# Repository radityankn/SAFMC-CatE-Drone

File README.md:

# SAFMC-CatE-Drone
A repository for SAFMC Cat E 2025 Drone Design. It consist of Hardware, Software, and Firmware file. The drone is incomplete though, as lack of funds and increased difficulty of development continue to prevent the team from completing it, leading to its early withdrawal from the competition

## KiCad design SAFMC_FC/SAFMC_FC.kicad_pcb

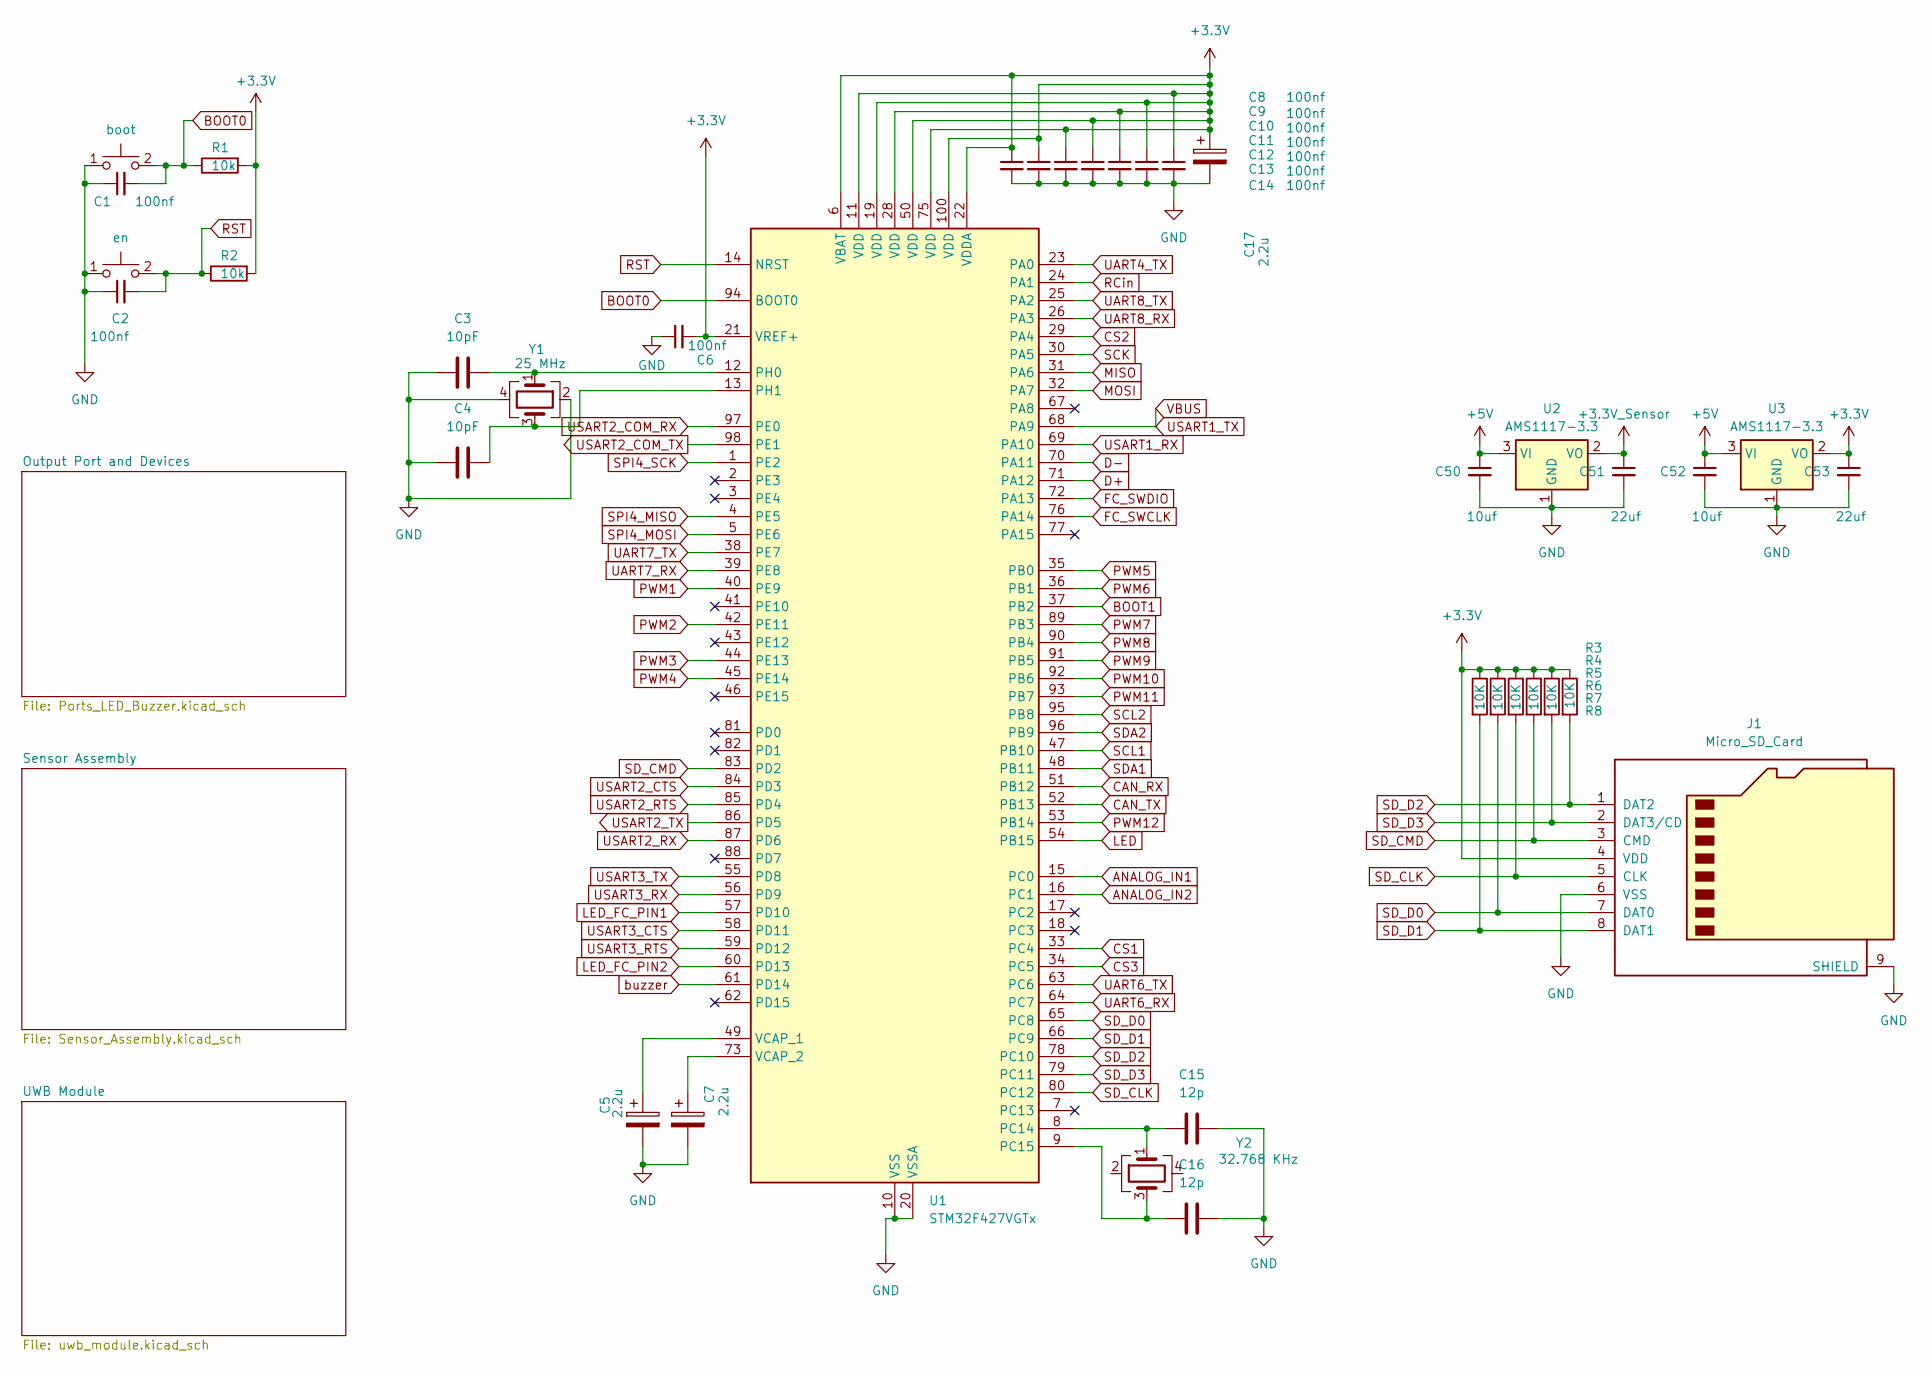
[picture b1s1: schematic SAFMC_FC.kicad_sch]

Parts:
C1, C2, C6, C8, C9, C10, C11, C12, C13, C14: 100nf; C_0603_1608Metric_Pad1.08x0.95mm_HandSolder
C3, C4: 10pF; C_0603_1608Metric_Pad1.08x0.95mm_HandSolder
C5, C7, C17: 2.2u; C_0603_1608Metric_Pad1.08x0.95mm_HandSolder
C15, C16: 12p; C_0603_1608Metric_Pad1.08x0.95mm_HandSolder
C50, C52: 10uf; C_0805_2012Metric_Pad1.18x1.45mm_HandSolder
C51, C53: 22uf; C_0805_2012Metric_Pad1.18x1.45mm_HandSolder
J1: Micro_SD_Card; microSD_HC_Hirose_DM3BT-DSF-PEJS
R1, R2: 10k; R_0603_1608Metric_Pad0.98x0.95mm_HandSolder
R3, R4, R5, R6, R7, R8: 10K; R_0603_1608Metric_Pad0.98x0.95mm_HandSolder
SW1: boot; SW_Push_SPST_NO_Alps_SKRK
SW2: en; SW_Push_SPST_NO_Alps_SKRK
U1: STM32F427VGTx; LQFP-100_14x14mm_P0.5mm
U2, U3: AMS1117-3.3; SOT-223-3_TabPin2
Y1: 25 MHz; Crystal_SMD_3225-4Pin_3.2x2.5mm_HandSoldering
Y2: 32.768 KHz; Crystal_SMD_SeikoEpson_MC306-4Pin_8.0x3.2mm

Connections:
+3.3V: C6.2, C8.1, C9.1, C10.1, C11.1, C12.1, C13.1, C14.1, C17.1, C53.1, J1.4 (VDD), R1.1, R2.1, R3.1, R4.1, R5.1, R6.1, R7.1, R8.1, U1.6 (VBAT), U1.11 (VDD), U1.19 (VDD), U1.21 (VREF+), U1.22 (VDDA), U1.28 (VDD), U1.50 (VDD), U1.75 (VDD), U1.100 (VDD), U3.2 (VO); also elsewhere on the board
+3.3V_Sensor: C51.1, U2.2 (VO); also elsewhere on the board
+5V: C50.1, C52.1, U2.3 (VI), U3.3 (VI); also elsewhere on the board
ANALOG_IN1: U1.15 (PC0)
ANALOG_IN2: U1.16 (PC1)
BOOT0: C1.2, R1.2, SW1.2 (D), U1.94 (BOOT0)
BOOT1: U1.37 (PB2)
CAN_RX: U1.51 (PB12)
CAN_TX: U1.52 (PB13)
CS1: U1.33 (PC4); also elsewhere on the board
CS2: U1.29 (PA4); also elsewhere on the board
CS3: U1.34 (PC5); also elsewhere on the board
D+: U1.71 (PA12); also elsewhere on the board
D-: U1.70 (PA11); also elsewhere on the board
FC_SWCLK: U1.76 (PA14)
FC_SWDIO: U1.72 (PA13)
GND: C1.1, C2.1, C3.1, C4.1, C5.2, C6.1, C7.2, C8.2, C9.2, C10.2, C11.2, C12.2, C13.2, C14.2, C15.1, C16.1, C17.2, C50.2, C51.2, C52.2, C53.2, J1.6 (VSS), J1.9 (SHIELD), J1.11, SW1.1 (C), SW2.1 (C), U1.10 (VSS), U1.20 (VSSA), U1.27 (VSS), U1.74 (VSS), U1.99 (VSS), U2.1 (GND), U3.1 (GND), Y1.2, Y1.4; also elsewhere on the board
LED: U1.54 (PB15); also elsewhere on the board
LED_FC_PIN1: U1.57 (PD10); also elsewhere on the board
LED_FC_PIN2: U1.60 (PD13); also elsewhere on the board
MISO: U1.31 (PA6); also elsewhere on the board
MOSI: U1.32 (PA7); also elsewhere on the board
unnamed: C15.2, U1.8 (PC14), Y2.1
unnamed: C16.2, U1.9 (PC15), Y2.3
unnamed: C3.2, U1.12 (PH0), Y1.1
unnamed: C4.2, U1.13 (PH1), Y1.3
unnamed: C5.1, U1.49 (VCAP_1)
unnamed: C7.1, U1.73 (VCAP_2)
PWM1: U1.40 (PE9); also elsewhere on the board
PWM2: U1.42 (PE11); also elsewhere on the board
PWM3: U1.44 (PE13); also elsewhere on the board
PWM4: U1.45 (PE14); also elsewhere on the board
PWM5: U1.35 (PB0); also elsewhere on the board
PWM6: U1.36 (PB1); also elsewhere on the board
PWM7: U1.89 (PB3)
PWM8: U1.90 (PB4)
PWM9: U1.91 (PB5)
PWM10: U1.92 (PB6)
PWM11: U1.93 (PB7)
PWM12: U1.53 (PB14)
RCin: U1.24 (PA1); also elsewhere on the board
RST: C2.2, R2.2, SW2.2 (D), U1.14 (NRST)
SCK: U1.30 (PA5); also elsewhere on the board
SCL1: U1.47 (PB10); also elsewhere on the board
SCL2: U1.95 (PB8)
SDA1: U1.48 (PB11); also elsewhere on the board
SDA2: U1.96 (PB9)
SD_CLK: J1.5 (CLK), R5.2, U1.80 (PC12)
SD_CMD: J1.3 (CMD), R6.2, U1.83 (PD2)
SD_D0: J1.7 (DAT0), R4.2, U1.65 (PC8)
SD_D1: J1.8 (DAT1), R3.2, U1.66 (PC9)
SD_D2: J1.1 (DAT2), R8.2, U1.78 (PC10)
SD_D3: J1.2 (DAT3/CD), R7.2, U1.79 (PC11)
SPI4_MISO: U1.4 (PE5)
SPI4_MOSI: U1.5 (PE6)
SPI4_SCK: U1.1 (PE2)
UART4_TX: U1.23 (PA0)
UART6_RX: U1.64 (PC7)
UART6_TX: U1.63 (PC6)
UART7_RX: U1.39 (PE8)
UART7_TX: U1.38 (PE7)
UART8_RX: U1.26 (PA3)
UART8_TX: U1.25 (PA2)
USART1_RX: U1.69 (PA10)
USART1_TX: U1.68 (PA9); also elsewhere on the board
USART2_COM_RX: U1.97 (PE0); also elsewhere on the board
USART2_COM_TX: U1.98 (PE1); also elsewhere on the board
USART2_CTS: U1.84 (PD3)
USART2_RTS: U1.85 (PD4)
USART2_RX: U1.87 (PD6)
USART2_TX: U1.86 (PD5)
USART3_CTS: U1.58 (PD11)
USART3_RTS: U1.59 (PD12)
USART3_RX: U1.56 (PD9)
USART3_TX: U1.55 (PD8)
buzzer: U1.61 (PD14); also elsewhere on the board

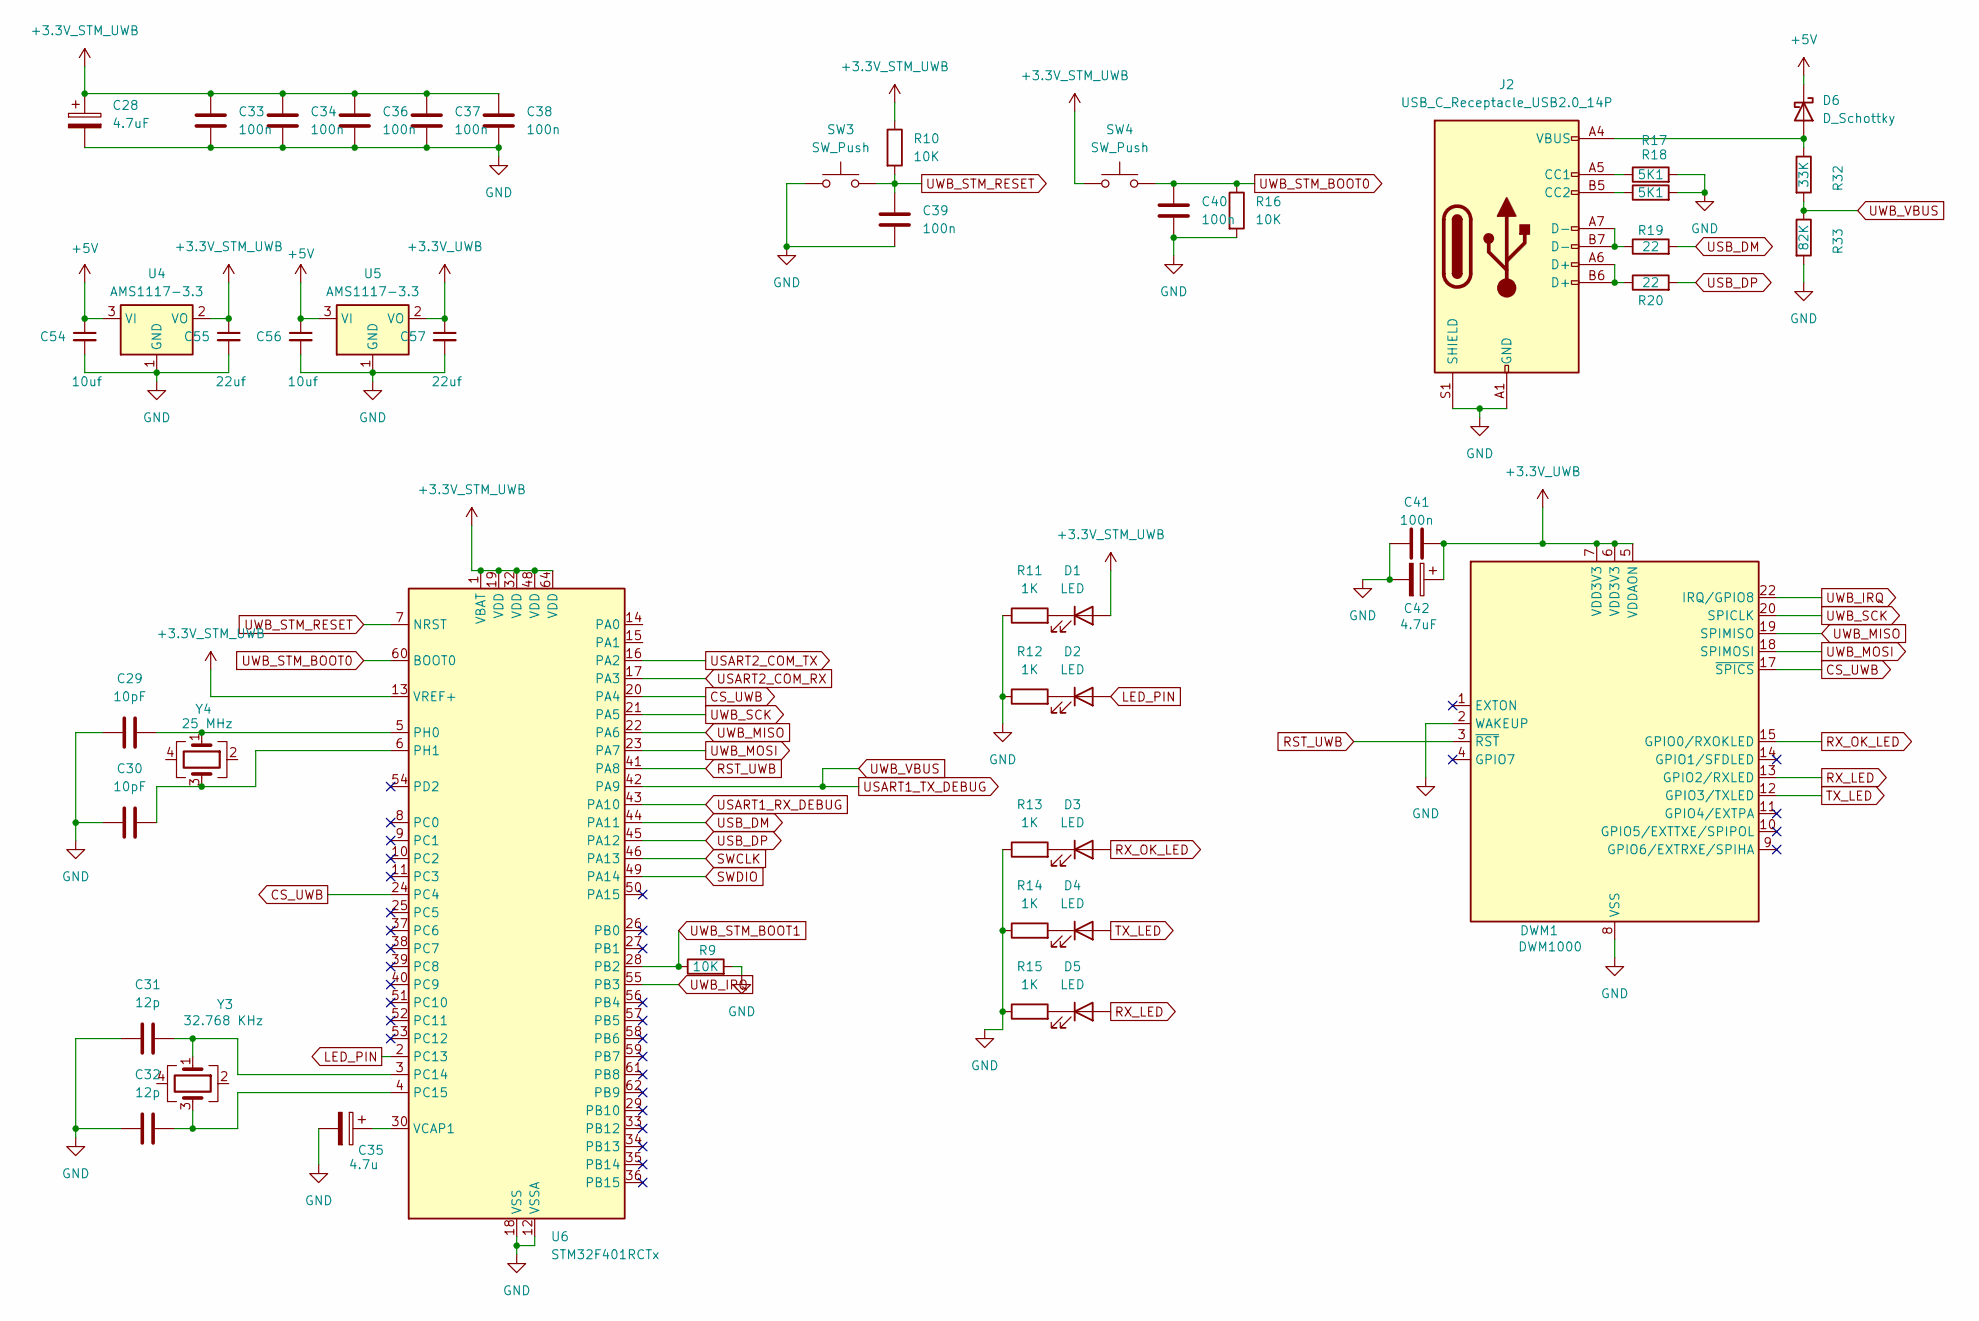
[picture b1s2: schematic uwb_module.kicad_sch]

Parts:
C28, C42: 4.7uF; C_0603_1608Metric_Pad1.08x0.95mm_HandSolder
C29, C30: 10pF; C_0603_1608Metric_Pad1.08x0.95mm_HandSolder
C31, C32: 12p; C_0603_1608Metric_Pad1.08x0.95mm_HandSolder
C33, C34, C36, C37, C38, C39, C40, C41: 100n; C_0603_1608Metric_Pad1.08x0.95mm_HandSolder
C35: 4.7u; C_0603_1608Metric_Pad1.08x0.95mm_HandSolder
C54, C56: 10uf; C_0805_2012Metric_Pad1.18x1.45mm_HandSolder
C55, C57: 22uf; C_0805_2012Metric_Pad1.18x1.45mm_HandSolder
D1, D2, D3, D4, D5: LED; LED_0603_1608Metric_Pad1.05x0.95mm_HandSolder
D6: D_Schottky; D_SOD-323F
DWM1: DWM1000
J2: USB_C_Receptacle_USB2.0_14P; USB_C_Receptacle_JAE_DX07S016JA1R1500
R9, R10, R16: 10K; R_0603_1608Metric_Pad0.98x0.95mm_HandSolder
R11, R12, R13, R14, R15: 1K; R_0603_1608Metric_Pad0.98x0.95mm_HandSolder
R17, R18: 5K1; R_0603_1608Metric_Pad0.98x0.95mm_HandSolder
R19, R20: 22; R_0603_1608Metric_Pad0.98x0.95mm_HandSolder
R32: 33K; R_0603_1608Metric_Pad0.98x0.95mm_HandSolder
R33: 82K; R_0603_1608Metric_Pad0.98x0.95mm_HandSolder
SW3, SW4: SW_Push; SW_Push_SPST_NO_Alps_SKRK
U4, U5: AMS1117-3.3; SOT-223-3_TabPin2
U6: STM32F401RCTx; LQFP-64_10x10mm_P0.5mm
Y3: 32.768 KHz; Crystal_SMD_SeikoEpson_MC306-4Pin_8.0x3.2mm
Y4: 25 MHz; Crystal_SMD_3225-4Pin_3.2x2.5mm_HandSoldering

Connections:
+3.3V_STM_UWB: C28.1, C33.2, C34.2, C36.2, C37.2, C38.2, C55.1, D1.2 (A), R10.1, SW4.1, U4.2 (VO), U6.1 (VBAT), U6.13 (VREF+), U6.19 (VDD), U6.32 (VDD), U6.48 (VDD), U6.64 (VDD)
+3.3V_UWB: C41.1, C42.1, C57.1, DWM1.5 (VDDAON), DWM1.6 (VDD3V3), DWM1.7 (VDD3V3), U5.2 (VO)
+5V: C54.1, C56.1, D6.1 (K), U4.3 (VI), U5.3 (VI); also elsewhere on the board
CS_UWB: DWM1.17 (~SPICS), U6.20 (PA4), U6.24 (PC4)
GND: C28.2, C29.1, C30.1, C31.1, C32.1, C33.1, C34.1, C35.2, C36.1, C37.1, C38.1, C39.1, C40.1, C41.2, C42.2, C54.2, C55.2, C56.2, C57.2, DWM1.2 (WAKEUP), DWM1.8 (VSS), DWM1.16 (VSS), DWM1.21 (VSS), DWM1.23 (VSS), DWM1.24 (VSS), J2.A1 (GND), J2.A12 (GND), J2.B1 (GND), J2.B12 (GND), J2.S1 (SHIELD), R9.2, R11.1, R12.1, R13.1, R14.1, R15.1, R16.2, R17.2, R18.2, R33.2, SW3.1, U4.1 (GND), U5.1 (GND), U6.12 (VSSA), U6.18 (VSS), U6.31 (VSS), U6.47 (VSS), U6.63 (VSS); also elsewhere on the board
LED_PIN: D2.2 (A), U6.2 (PC13)
unnamed: D1.1 (K), R11.2
unnamed: D2.1 (K), R12.2
unnamed: D3.1 (K), R13.2
unnamed: D4.1 (K), R14.2
unnamed: D5.1 (K), R15.2
unnamed: D6.2 (A), J2.A4 (VBUS), J2.A9 (VBUS), J2.B4 (VBUS), J2.B9 (VBUS), R32.1
unnamed: J2.A5 (CC1), R17.1
unnamed: J2.B5 (CC2), R18.1
unnamed: J2.A6 (D+), J2.B6 (D+), R20.1
unnamed: J2.A7 (D-), J2.B7 (D-), R19.1
unnamed: C31.2, U6.3 (PC14), Y3.1
unnamed: C32.2, U6.4 (PC15), Y3.3
unnamed: C29.2, U6.5 (PH0), Y4.1
unnamed: C30.2, U6.6 (PH1), Y4.3
unnamed: C35.1, U6.30 (VCAP1)
RST_UWB: DWM1.3 (~RST), U6.41 (PA8)
RX_LED: D5.2 (A), DWM1.13 (GPIO2/RXLED)
RX_OK_LED: D3.2 (A), DWM1.15 (GPIO0/RXOKLED)
SWCLK: U6.46 (PA13)
SWDIO: U6.49 (PA14)
TX_LED: D4.2 (A), DWM1.12 (GPIO3/TXLED)
USART1_RX_DEBUG: U6.43 (PA10)
USART1_TX_DEBUG: R32.2, R33.1, U6.42 (PA9)
USART2_COM_RX: U6.17 (PA3); also elsewhere on the board
USART2_COM_TX: U6.16 (PA2); also elsewhere on the board
USB_DM: R19.2, U6.44 (PA11)
USB_DP: R20.2, U6.45 (PA12)
UWB_IRQ: DWM1.22 (IRQ/GPIO8), U6.55 (PB3)
UWB_MISO: DWM1.19 (SPIMISO), U6.22 (PA6)
UWB_MOSI: DWM1.18 (SPIMOSI), U6.23 (PA7)
UWB_SCK: DWM1.20 (SPICLK), U6.21 (PA5)
UWB_STM_BOOT0: C40.2, R16.1, SW4.2, U6.60 (BOOT0)
UWB_STM_BOOT1: R9.1, U6.28 (PB2)
UWB_STM_RESET: C39.2, R10.2, SW3.2, U6.7 (NRST)

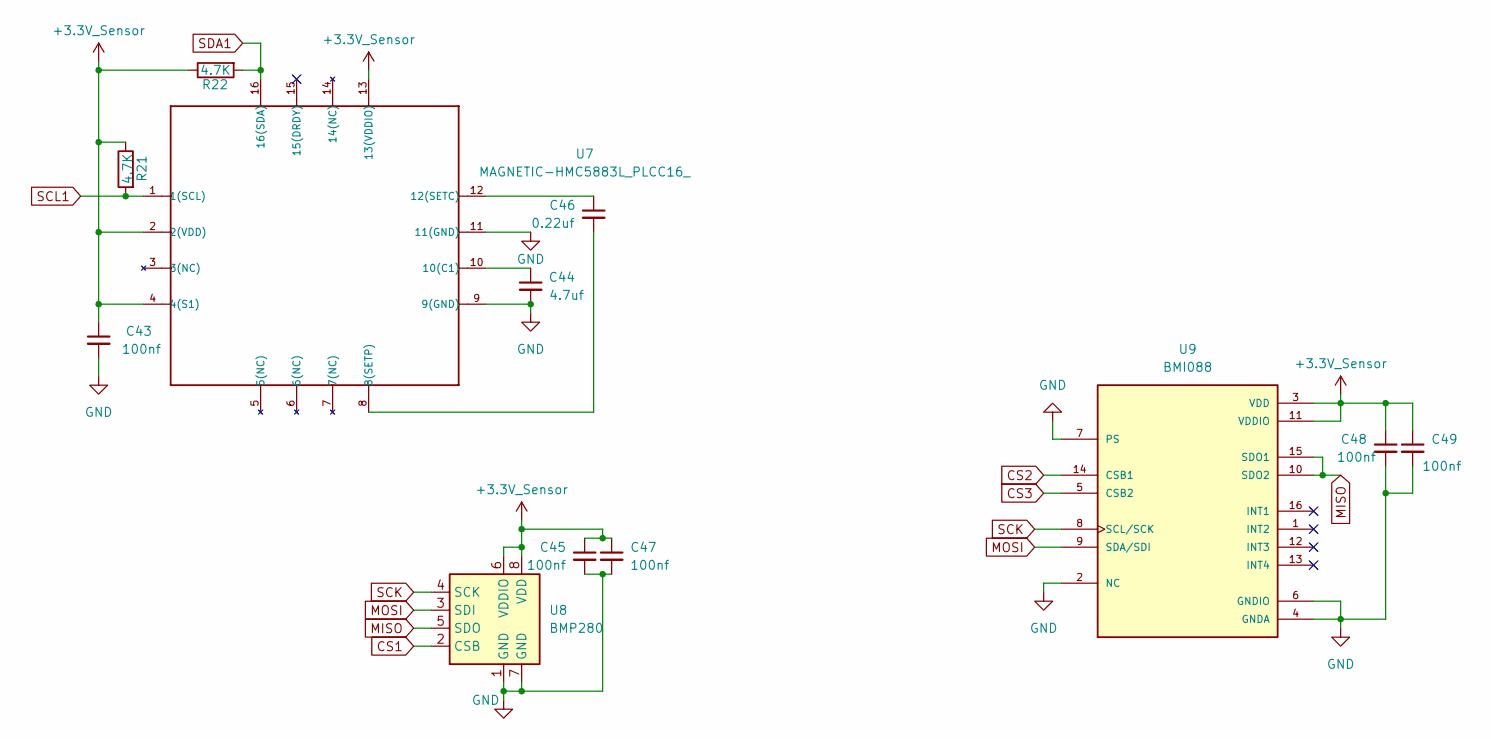
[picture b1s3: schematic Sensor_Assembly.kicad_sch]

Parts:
C43, C45, C47, C48, C49: 100nf; C_0603_1608Metric_Pad1.08x0.95mm_HandSolder
C44: 4.7uf; C_0603_1608Metric_Pad1.08x0.95mm_HandSolder
C46: 0.22uf; C_0805_2012Metric_Pad1.18x1.45mm_HandSolder
R21, R22: 4.7K; R_0603_1608Metric_Pad0.98x0.95mm_HandSolder
U7: MAGNETIC-HMC5883L_PLCC16_; PLCC16-0.5-3X3MM; MPN HMC5883L
U8: BMP280; Bosch_LGA-8_2x2.5mm_P0.65mm_ClockwisePinNumbering
U9: BMI088; PQFN50P450X300X100-16N

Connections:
+3.3V_Sensor: C43.1, C45.1, C47.1, C48.1, C49.1, R21.2, R22.2, U7.2 (2(VDD)), U7.4 (4(S1)), U7.13 (13(VDDIO)), U8.6 (VDDIO), U8.8 (VDD), U9.3 (VDD), U9.11 (VDDIO); also elsewhere on the board
CS1: U8.2 (CSB); also elsewhere on the board
CS2: U9.14 (CSB1); also elsewhere on the board
CS3: U9.5 (CSB2); also elsewhere on the board
GND: C43.2, C44.2, C45.2, C47.2, C48.2, C49.2, U7.9 (9(GND)), U7.11 (11(GND)), U8.1 (GND), U8.7 (GND), U9.2 (NC), U9.4 (GNDA), U9.6 (GNDIO), U9.7 (PS); also elsewhere on the board
MISO: U8.5 (SDO), U9.10 (SDO2), U9.15 (SDO1); also elsewhere on the board
MOSI: U8.3 (SDI), U9.9 (SDA/SDI); also elsewhere on the board
unnamed: C46.2, U7.8 (8(SETP))
unnamed: C44.1, U7.10 (10(C1))
unnamed: C46.1, U7.12 (12(SETC))
SCK: U8.4 (SCK), U9.8 (SCL/SCK); also elsewhere on the board
SCL1: R21.1, U7.1 (1(SCL)); also elsewhere on the board
SDA1: R22.1, U7.16 (16(SDA)); also elsewhere on the board

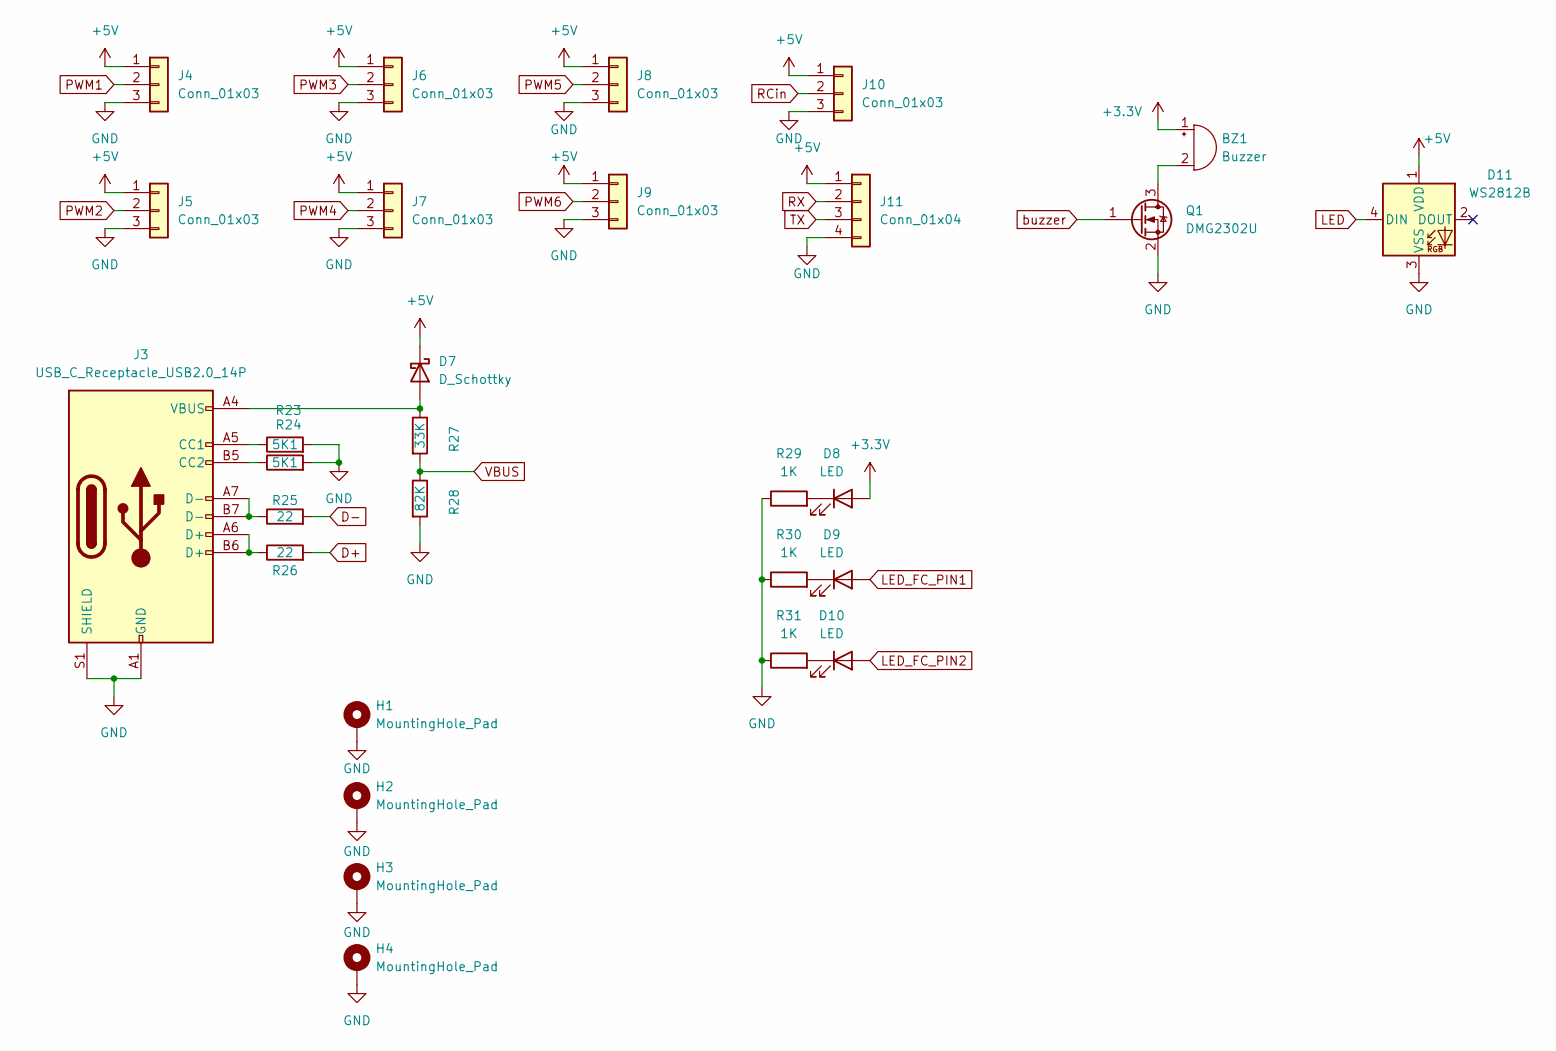
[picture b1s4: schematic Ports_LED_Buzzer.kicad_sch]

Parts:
BZ1: Buzzer
D7: D_Schottky; D_SOD-323F
D8, D9, D10: LED; LED_0603_1608Metric_Pad1.05x0.95mm_HandSolder
D11: WS2812B; LED_WS2812B_PLCC4_5.0x5.0mm_P3.2mm
H1, H2, H3, H4: MountingHole_Pad; MountingHole_2.7mm_M2.5_Pad
J3: USB_C_Receptacle_USB2.0_14P; USB_C_Receptacle_JAE_DX07S016JA1R1500
J4, J5, J6, J7, J8, J9, J10: Conn_01x03; PinHeader_1x03_P2.54mm_Vertical; Part Number 1-0301FBV0T
J11: Conn_01x04; JST_XH_B4B-XH-A_1x04_P2.50mm_Vertical; Part Number 1-0401FBV0T
Q1: DMG2302U; SOT-23
R23, R24: 5K1; R_0603_1608Metric_Pad0.98x0.95mm_HandSolder
R25, R26: 22; R_0603_1608Metric_Pad0.98x0.95mm_HandSolder
R27: 33K; R_0603_1608Metric_Pad0.98x0.95mm_HandSolder
R28: 82K; R_0603_1608Metric_Pad0.98x0.95mm_HandSolder
R29, R30, R31: 1K; R_0603_1608Metric_Pad0.98x0.95mm_HandSolder

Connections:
+3.3V: BZ1.1 (+), D8.2 (A); also elsewhere on the board
+5V: D7.1 (K), D11.1 (VDD), J4.1, J5.1, J6.1, J7.1, J8.1, J9.1, J10.1, J11.1; also elsewhere on the board
D+: R26.2; also elsewhere on the board
D-: R25.2; also elsewhere on the board
GND: D11.3 (VSS), H1.1, H2.1, H3.1, H4.1, J3.A1 (GND), J3.A12 (GND), J3.B1 (GND), J3.B12 (GND), J3.S1 (SHIELD), J4.3, J5.3, J6.3, J7.3, J8.3, J9.3, J10.3, J11.4, Q1.2 (S), R23.2, R24.2, R28.2, R29.1, R30.1, R31.1; also elsewhere on the board
LED: D11.4 (DIN); also elsewhere on the board
LED_FC_PIN1: D9.2 (A); also elsewhere on the board
LED_FC_PIN2: D10.2 (A); also elsewhere on the board
unnamed: BZ1.2 (-), Q1.3 (D)
unnamed: D7.2 (A), J3.A4 (VBUS), J3.A9 (VBUS), J3.B4 (VBUS), J3.B9 (VBUS), R27.1
unnamed: D8.1 (K), R29.2
unnamed: D9.1 (K), R30.2
unnamed: D10.1 (K), R31.2
unnamed: J3.A5 (CC1), R23.1
unnamed: J3.B5 (CC2), R24.1
unnamed: J3.A6 (D+), J3.B6 (D+), R26.1
unnamed: J3.A7 (D-), J3.B7 (D-), R25.1
PWM1: J4.2; also elsewhere on the board
PWM2: J5.2; also elsewhere on the board
PWM3: J6.2; also elsewhere on the board
PWM4: J7.2; also elsewhere on the board
PWM5: J8.2; also elsewhere on the board
PWM6: J9.2; also elsewhere on the board
RCin: J10.2; also elsewhere on the board
RX: J11.2
TX: J11.3
USART1_TX: R27.2, R28.1; also elsewhere on the board
buzzer: Q1.1 (G); also elsewhere on the board

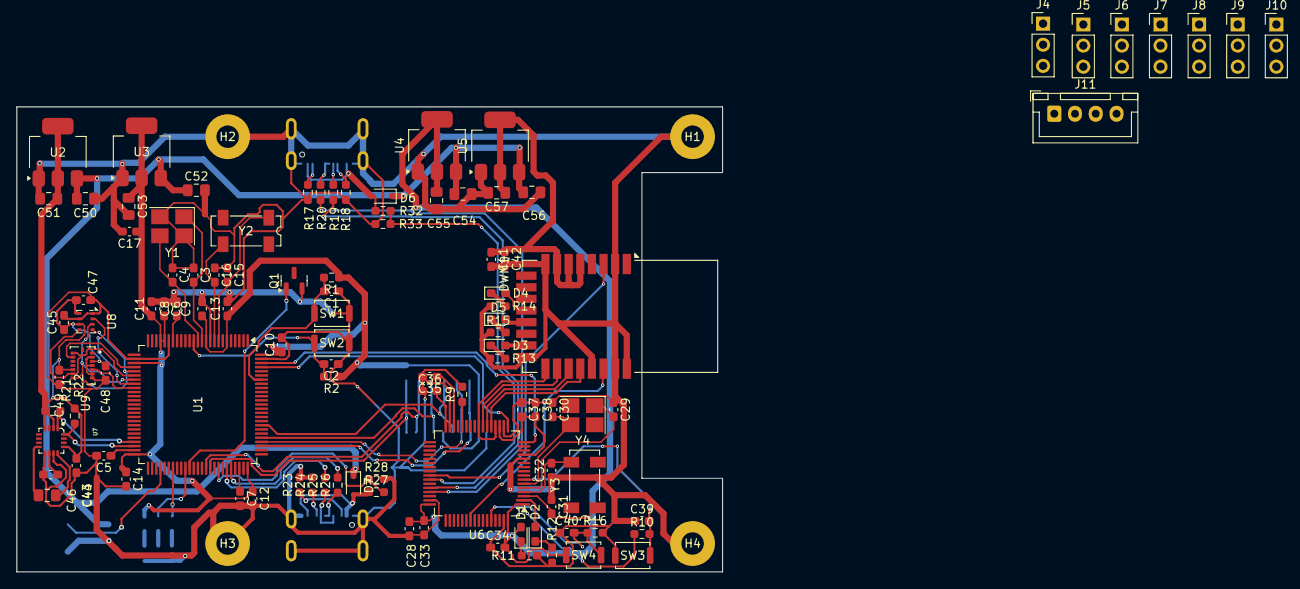
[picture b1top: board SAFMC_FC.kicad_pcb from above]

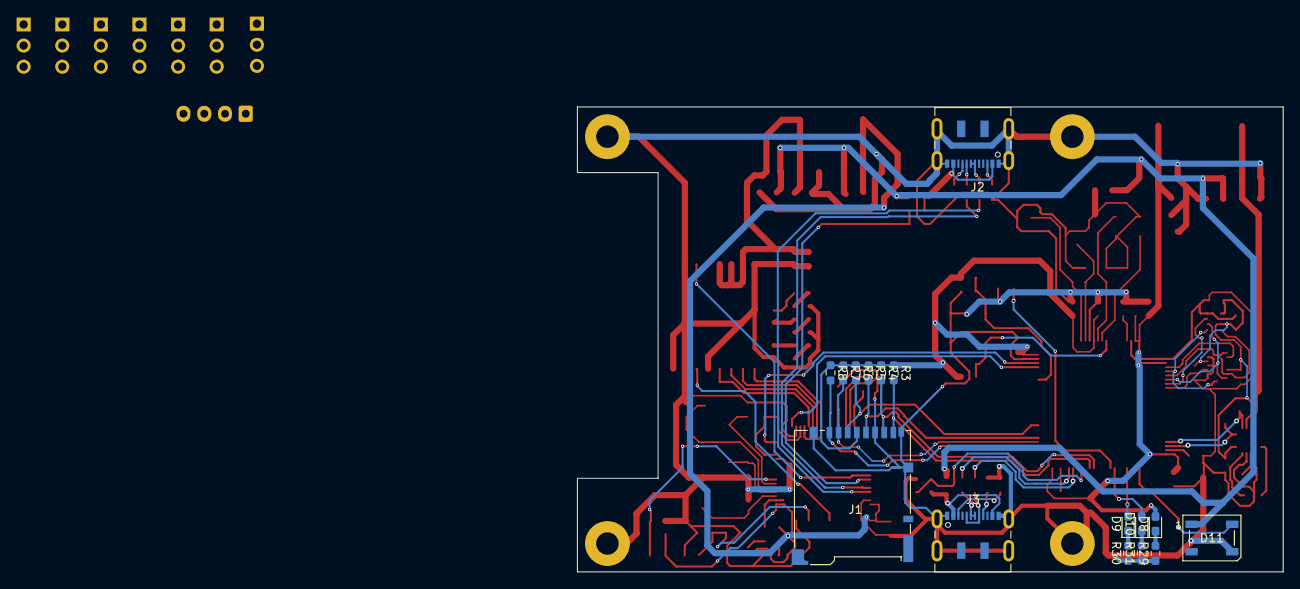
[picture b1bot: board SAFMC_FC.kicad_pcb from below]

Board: 4 copper layers, 85.0 x 56.0 mm, 125 parts (16 on the bottom side), 86 nets.
